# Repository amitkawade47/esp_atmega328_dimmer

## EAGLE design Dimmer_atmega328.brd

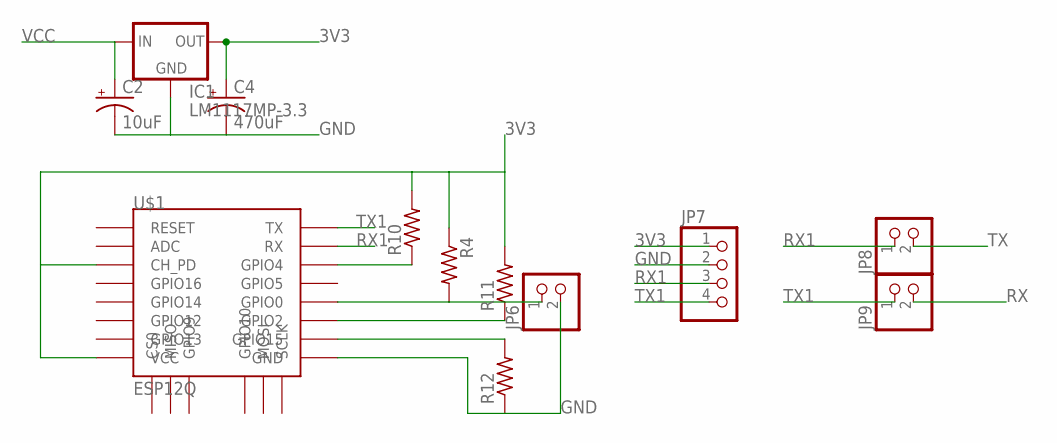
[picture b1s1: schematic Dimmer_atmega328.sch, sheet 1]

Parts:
C2: 10uF; E2,5-6
C4: 470uF; E5-8,5
IC1: LM1117MP-3.3; SOT223
JP6, JP8, JP9: PINHD-1X2; 1X02
JP7: PINHD-1X4; 1X04
R4, R10, R11, R12: R-US_0207/10; 0207/10
U$1: ESP12Q

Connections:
3V3: C4.+, IC1.2 (OUT), IC1.4 (OUT), JP7.1, R4.1, R10.2, R11.2, U$1.CH_PD, U$1.VCC
GND: C2.-, C4.-, IC1.1 (GND), JP6.2, JP7.2, R12.1, U$1.GND; also elsewhere on the board
unnamed: JP6.1, R4.2, U$1.GPIO0
unnamed: R10.1, U$1.GPIO4
unnamed: R11.1, U$1.GPIO2
unnamed: R12.2, U$1.GPIO15
RX: JP9.2; also elsewhere on the board
RX1: JP7.3, JP8.1, U$1.RX
TX: JP8.2; also elsewhere on the board
TX1: JP7.4, JP9.1, U$1.TX
VCC: C2.+, IC1.3 (IN); also elsewhere on the board

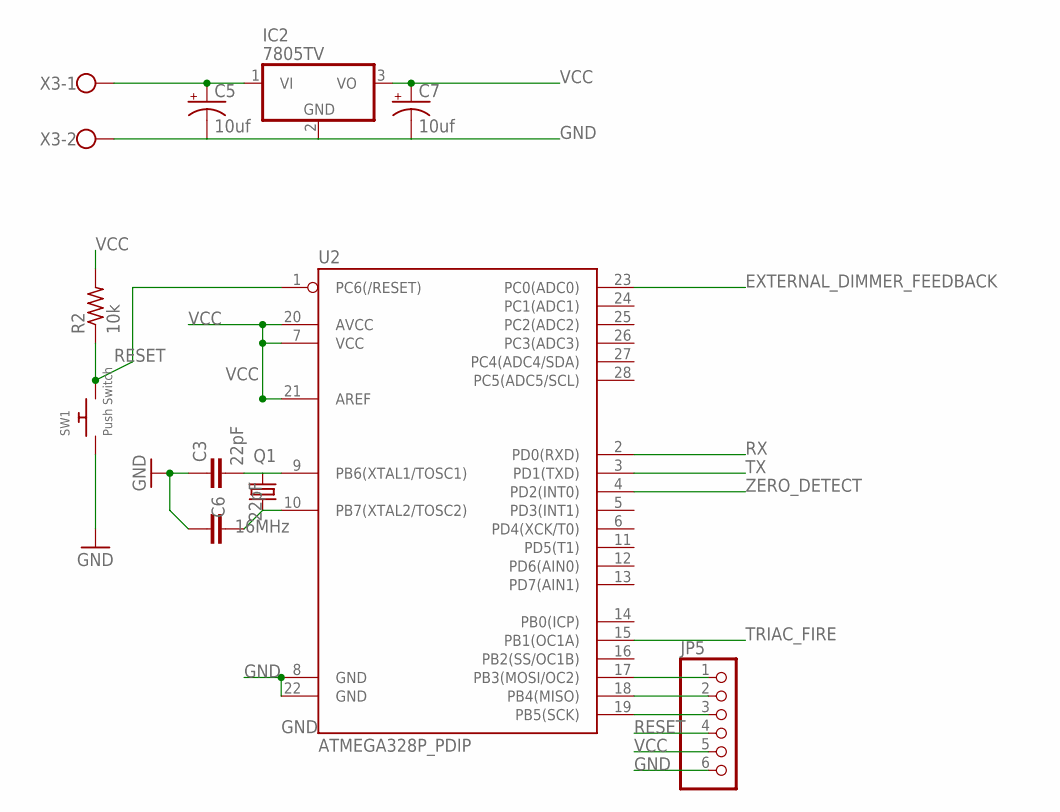
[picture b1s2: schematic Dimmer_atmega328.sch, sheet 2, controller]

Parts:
C3, C6: 22pF; CAP-PTH-SMALL
C5, C7: 10uf; E2,5-6
IC2: 7805TV; TO220V
JP5: PINHD-1X6; 1X06
Q1: 16MHz; HC49US
R2: 10k; 0207/10
SW1: Push Switch; TACT_PANA-EVQ
U2: ATMEGA328P_PDIP; DIL28-3
X3: W237-102

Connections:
EXTERNAL_DIMMER_FEEDBACK: U2.23 (PC0(ADC0)); also elsewhere on the board
GND: C3.1, C5.-, C6.1, C7.-, IC2.2 (GND), JP5.6, SW1.P$1, U2.8 (GND), U2.22 (GND), X3.2; also elsewhere on the board
unnamed: JP5.3, U2.19 (PB5(SCK))
unnamed: JP5.2, U2.18 (PB4(MISO))
unnamed: JP5.1, U2.17 (PB3(MOSI/OC2))
unnamed: C3.2, Q1.2, U2.9 (PB6(XTAL1/TOSC1))
unnamed: C6.2, Q1.1, U2.10 (PB7(XTAL2/TOSC2))
unnamed: C5.+, IC2.1 (VI), X3.1
RESET: JP5.4, R2.1, SW1.P$2, U2.1 (PC6(/RESET))
RX: U2.2 (PD0(RXD)); also elsewhere on the board
TRIAC_FIRE: U2.15 (PB1(OC1A)); also elsewhere on the board
TX: U2.3 (PD1(TXD)); also elsewhere on the board
VCC: C7.+, IC2.3 (VO), JP5.5, R2.2, U2.7 (VCC), U2.20 (AVCC), U2.21 (AREF); also elsewhere on the board
ZERO_DETECT: U2.4 (PD2(INT0)); also elsewhere on the board

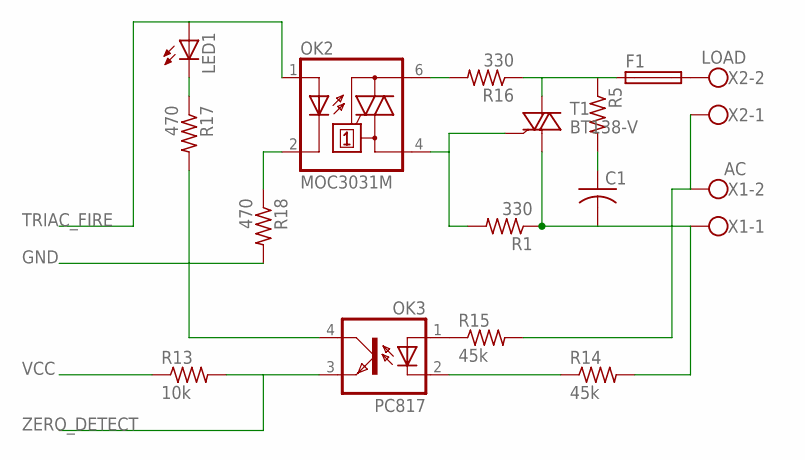
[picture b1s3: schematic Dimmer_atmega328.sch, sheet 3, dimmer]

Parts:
C1: C-US150-091X182; C150-091X182
F1: GSH15
LED1: LED3MM
OK2: MOC3031M; DIL06
OK3: PC817; DIL04
R1, R16: 330; 0207/10
R5: R-US_0411/15; 0411/15
R13: 10k; 0207/10
R14, R15: 45k; 0207/10
R17, R18: 470; 0207/10
T1: BT138-V; TO220BV
X1: AC; W237-102
X2: LOAD; W237-102

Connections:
GND: OK3.4 (COL), R17.2, R18.2; also elsewhere on the board
unnamed: OK3.1 (A), R15.1
unnamed: LED1.K (C), R17.1
unnamed: OK2.2 (C), R18.1
unnamed: OK2.6 (A2), R16.2
unnamed: C1.1, R5.2
unnamed: F1.1, R5.1, R16.1, T1.T2 (A2)
unnamed: R15.2, X1.2, X2.1
unnamed: C1.2, R1.1, R14.2, T1.T1 (A1), X1.1
unnamed: OK2.4 (A1), R1.2, T1.G
unnamed: F1.2, X2.2
unnamed: OK3.2 (C), R14.1
TRIAC_FIRE: LED1.A, OK2.1 (A); also elsewhere on the board
VCC: R13.1; also elsewhere on the board
ZERO_DETECT: OK3.3 (EMIT), R13.2; also elsewhere on the board

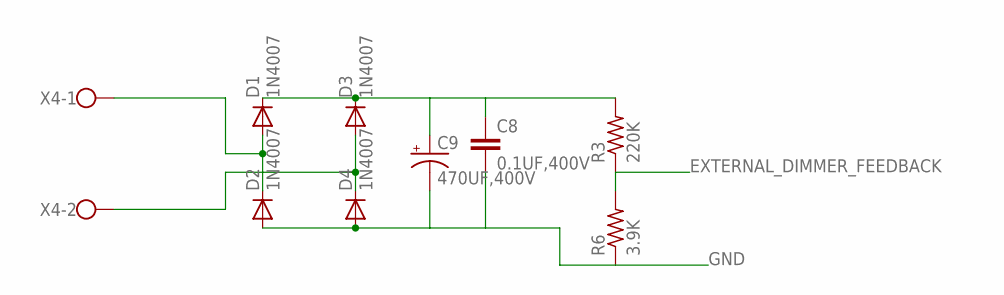
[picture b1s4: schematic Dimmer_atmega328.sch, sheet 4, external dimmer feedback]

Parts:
C8: 0.1UF,400V; C102-054X133
C9: 470UF,400V; E7,5-18
D1, D2, D3, D4: 1N4007; DO41-10
R3: 220K; 0207/10
R6: 3.9K; 0207/10
X4: W237-102

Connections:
EXTERNAL_DIMMER_FEEDBACK: R3.1, R6.2; also elsewhere on the board
GND: C8.2, C9.-, D2.A, D4.A, R6.1; also elsewhere on the board
unnamed: D1.A, D2.C, X4.1
unnamed: D3.A, D4.C, X4.2
unnamed: C8.1, C9.+, D1.C, D3.C, R3.2

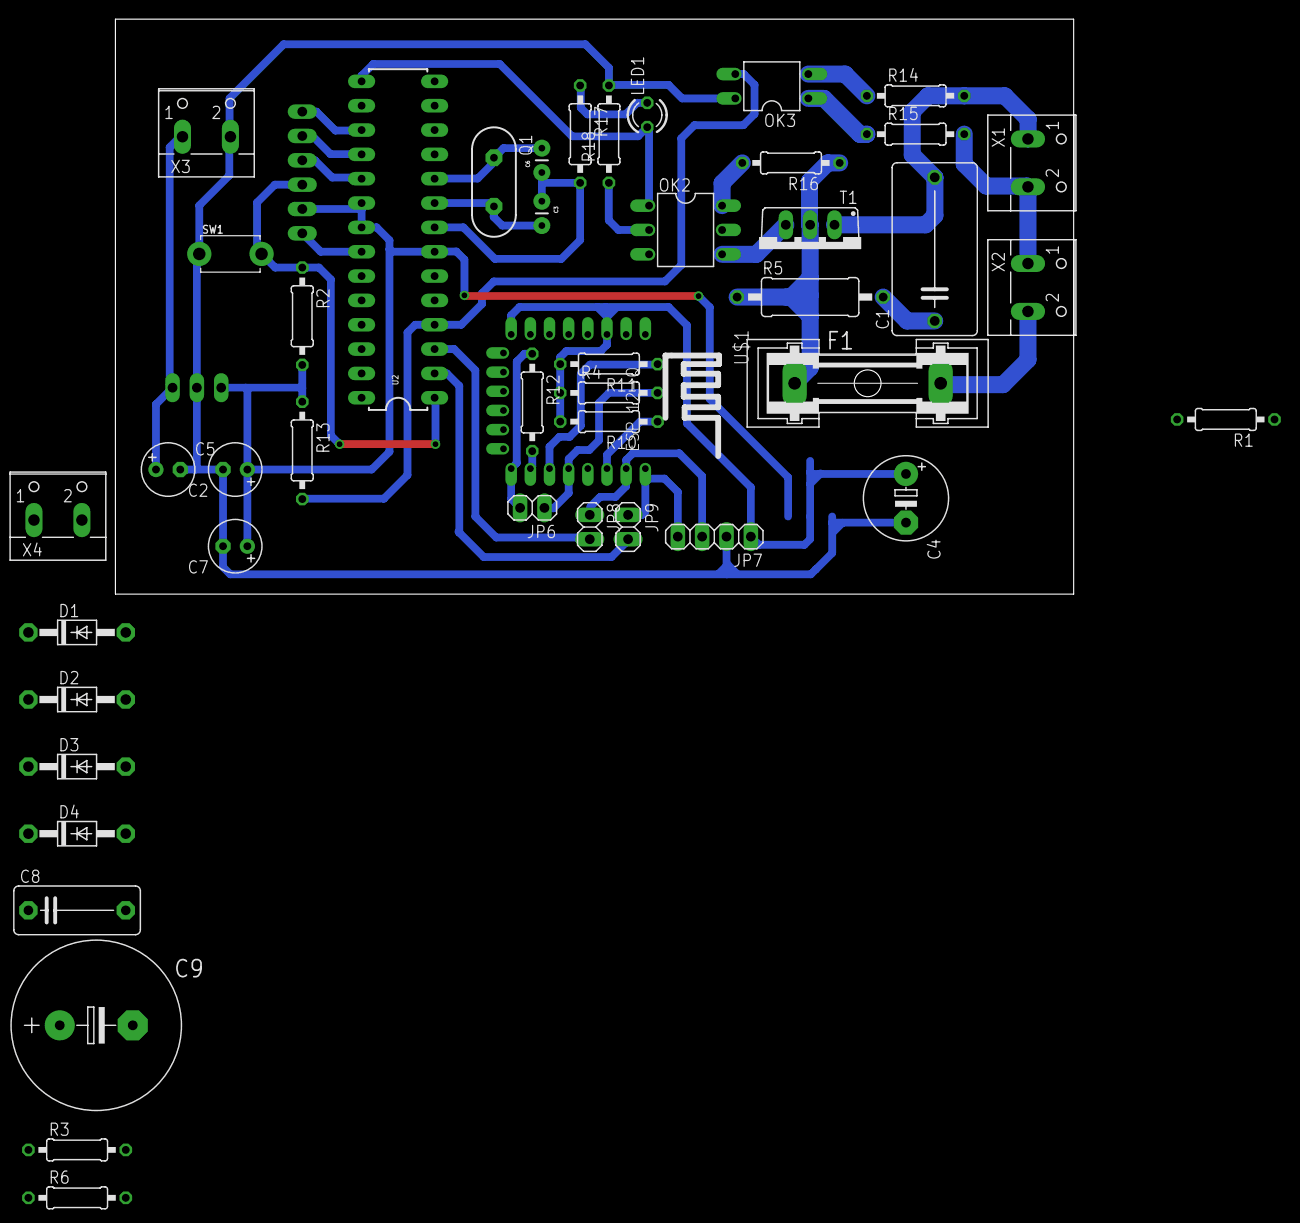
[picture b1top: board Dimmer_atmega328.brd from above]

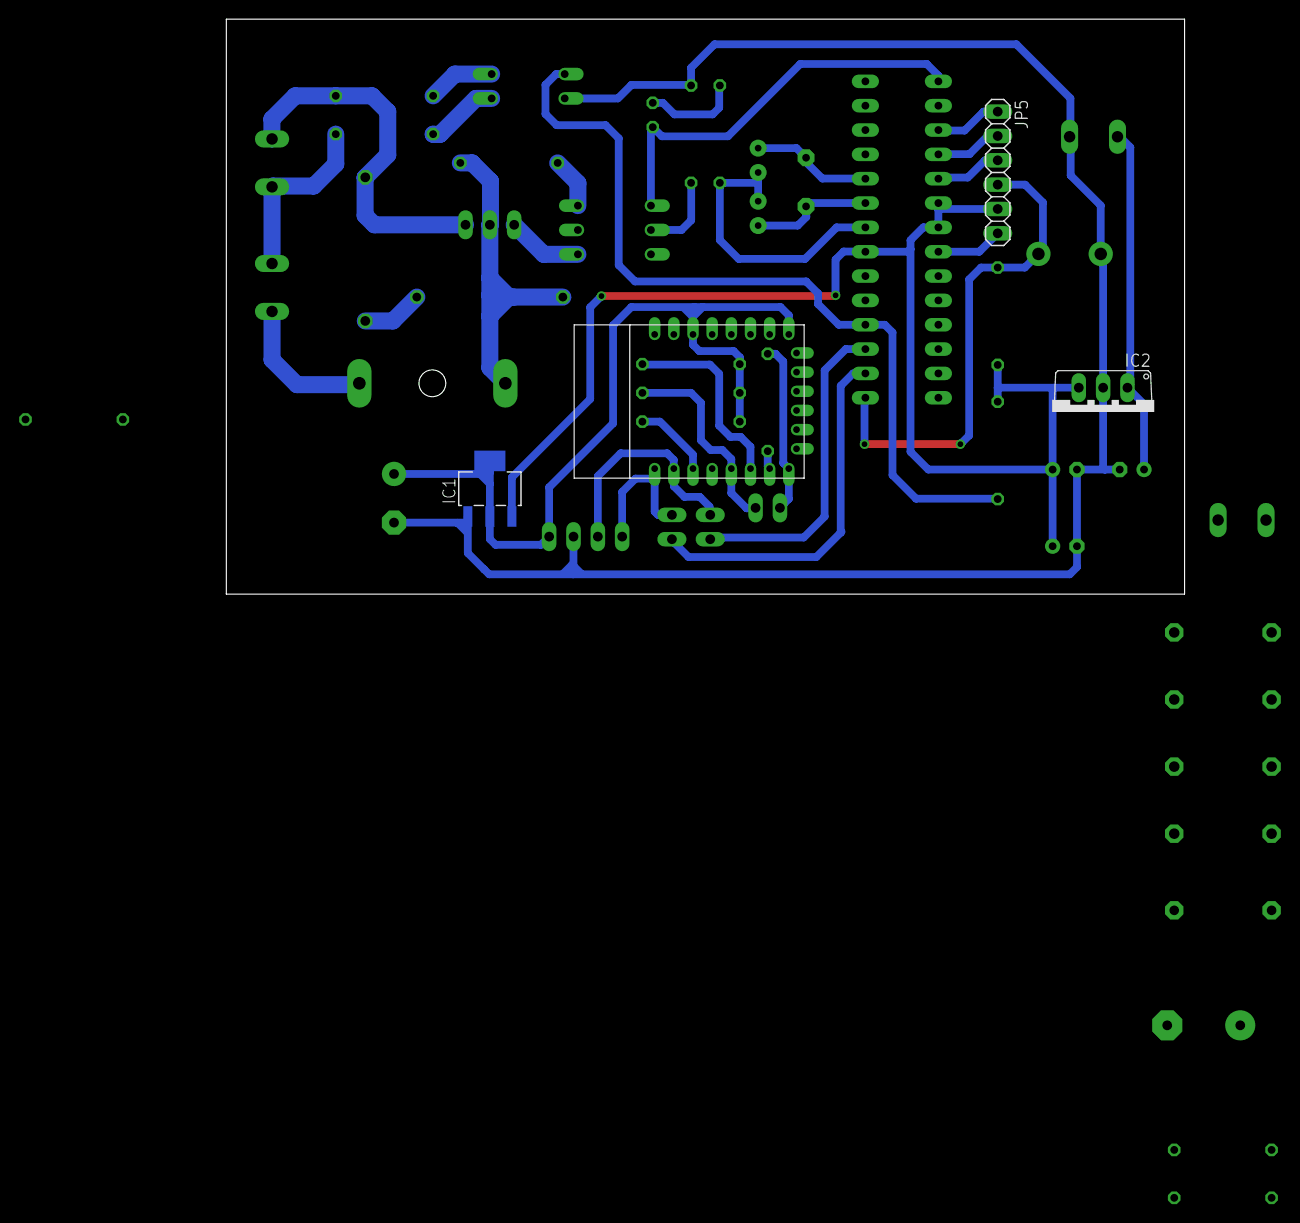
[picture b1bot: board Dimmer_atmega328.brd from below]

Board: 2 copper layers, 100.0 x 60.0 mm, 48 parts (3 on the bottom side), 35 nets.

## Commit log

2018-02-24 esp_atmega328_dimmer
    10x6 cm pcb layout
2018-02-24 routing 80% completed
2018-02-27 added resistor
    added resistor at gate of TRIAC
2018-02-27 routing
    single layer routing in progress
2018-03-15 external dimmer feedback
    external dimmer feedback circuit added.
    diode bridge with filter and devider circuit included in schematic

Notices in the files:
parts and their libraries:
SparkFun-DigitalIC: Licensing: Creative Commons ShareAlike 4.0 International - https://creativecommons.org/licenses/by-sa/4.0
